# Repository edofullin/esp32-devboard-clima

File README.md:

# ESP32-Clima

This repository contains the design and production files that I used to build by own ESP32-based OpenTherm* and ON/OFF thermostats.

The devices is based on a ESP32-S3 microcontroller, and can include *exclusively* a OpenTherm driver circuit or a latching on/off relay to drive the boiler. 
Optionally, a BME280 sensor can be soldered onto the board in order to measure temperature, humidity and pressure (and use them for control).

## Schematic

## PCB Design

## Final Result (OpenTherm version, no BME280)

Mounted by me by hand, imperfect but functioning. 

## Disclaimers

I'm an not a PCB designer / electronics professional, everything here is provided for free and the user assumes all resposibilities of what they do with the material.
This material comes AS-IS with ABSOLUTELY NO WARRANTY.

*I'm **NOT** affiliated with the [OpenTherm Association](https://www.opentherm.eu/) in any way, the circuit has **only** been tested by me on my own boiler and is not guaranteed to work on every boiler.

The OpenTherm circuit part is heavily inspired by [this](https://electronics.stackexchange.com/questions/466720/how-does-this-circuit-work-opentherm) StackExchange post.

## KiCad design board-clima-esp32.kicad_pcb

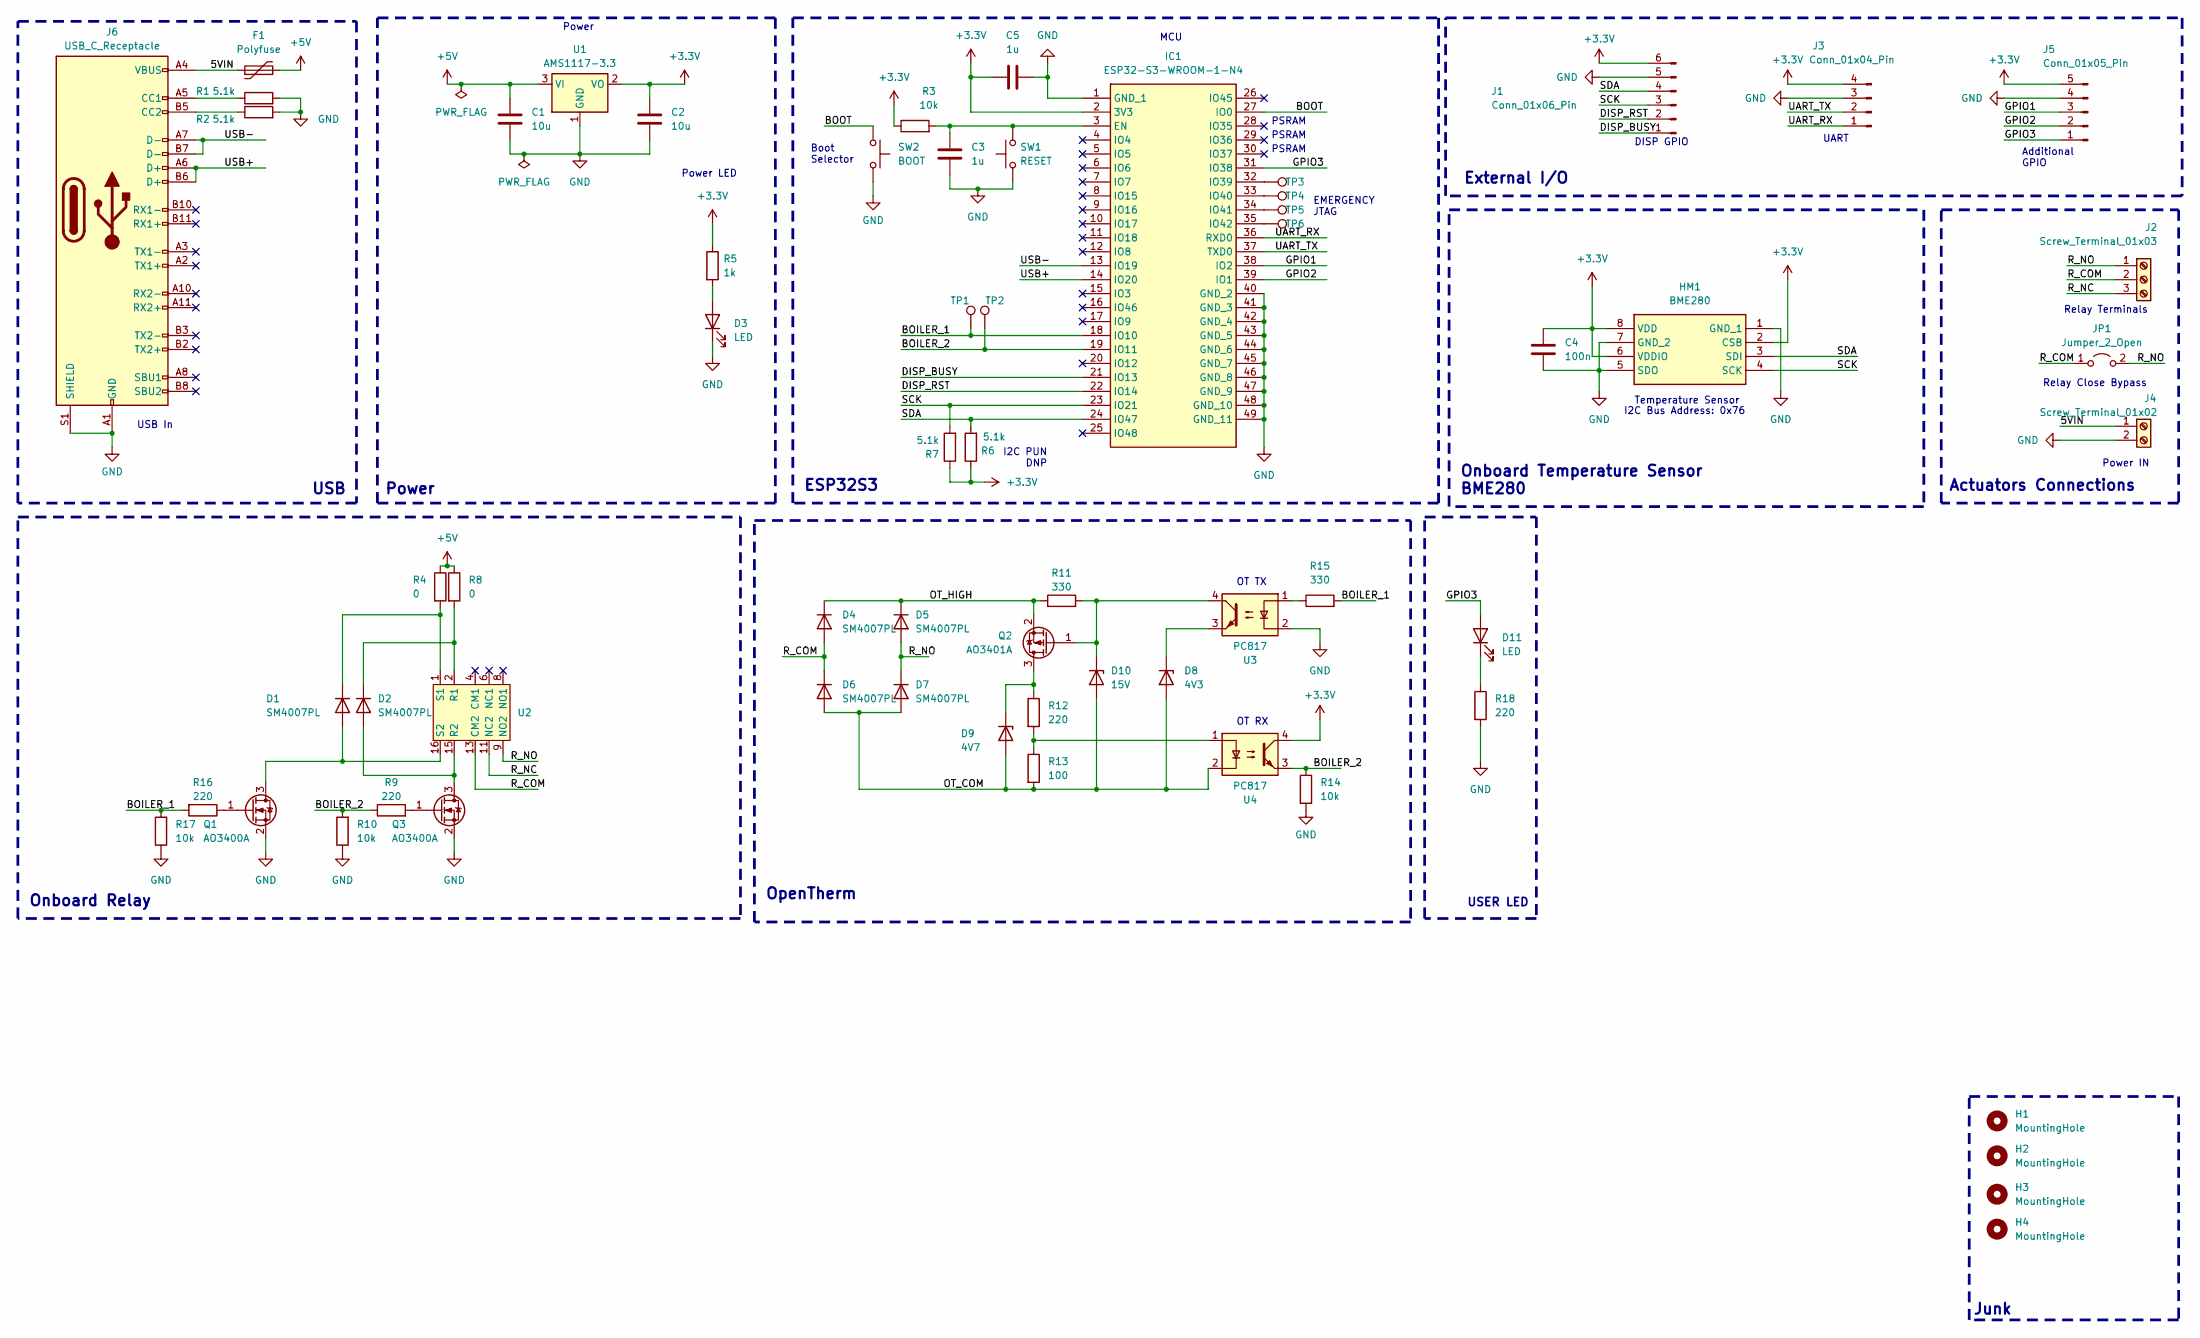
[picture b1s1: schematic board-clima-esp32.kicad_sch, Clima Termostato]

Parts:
C1, C2: 10u; C_0805_2012Metric; Manufacturer_Part_Number CL21A106KAYNNNE; LCSC C15850
C3: 1u; C_0805_2012Metric; Manufacturer_Part_Number CL21B105KBFNNNE; LCSC C28323
C4: 100n; C_0805_2012Metric; Manufacturer_Part_Number CC0805KRX7R9BB104; LCSC C49678
C5: 1u; C_0805_2012Metric
D1, D2, D4, D5, D6, D7: SM4007PL; D_SOD-123F
D3: LED; LED_0805_2012Metric; Manufacturer_Part_Number NCD0805R1; LCSC C84256
D8: 4V3; D_SOD-123
D9: 4V7; D_SOD-123
D10: 15V; D_SOD-123
D11: LED; LED_0805_2012Metric
F1: Polyfuse; Fuse_1812_4532Metric_Pad1.30x3.40mm_HandSolder; Manufacturer_Part_Number BSMD1812-200-30V; LCSC C960026
H1, H2, H3, H4: MountingHole; MountingHole_2.5mm
HM1: BME280; Mouser Part Number 262-BME280
IC1: ESP32-S3-WROOM-1-N4; ESP32S3WROOM1N8R8; Mouser Part Number 356-EP32S3WROOM1N8R8
J1: Conn_01x06_Pin; PinHeader_1x06_P2.54mm_Vertical
J2: Screw_Terminal_01x03; XYEK500-5.08-3P; Manufacturer_Part_Number XYEK500-5.08-3P
J3: Conn_01x04_Pin; PinHeader_1x04_P2.54mm_Vertical
J4: Screw_Terminal_01x02; XYEK500-5.08-2P
J5: Conn_01x05_Pin; PinHeader_1x05_P2.54mm_Vertical
J6: USB_C_Receptacle; HRO_TYPE-C-31-M-12; Manufacturer_Part_Number TYPE-C-31-M-12; LCSC C165948
JP1: Jumper_2_Open; TestPoint_2Pads_Pitch2.54mm_Drill0.8mm
Q1, Q3: AO3400A; SOT-23
Q2: AO3401A; SOT-23
R1, R2, R6, R7: 5.1k; R_0805_2012Metric; Manufacturer_Part_Number 0805W8F5101T5E; LCSC C17673
R3: 10k; R_0805_2012Metric; Manufacturer_Part_Number 0805W8F1002T5E; LCSC C17414
R4, R8: 0; R_0805_2012Metric
R5: 1k; R_0805_2012Metric; Manufacturer_Part_Number 0805W8F2200T5E; LCSC C17557
R9, R12, R16, R18: 220; R_0805_2012Metric
R10, R14, R17: 10k; R_0805_2012Metric
R11, R15: 330; R_0805_2012Metric
R13: 100; R_0805_2012Metric
SW1: RESET; SW_Push_1P1T_XKB_TS-1187A; Manufacturer_Part_Number TS-1187A-B-A-B; LCSC C318884
SW2: BOOT; SW_Push_1P1T_XKB_TS-1187A; Manufacturer_Part_Number TS-1187A-B-A-B; LCSC C318884
TP1, TP2, TP3, TP4, TP5, TP6: TestPoint; TestPoint_Pad_D1.0mm
U1: AMS1117-3.3; SOT-223-3_TabPin2; Manufacturer_Part_Number 0805W8F5101T5E; LCSC C6186
U2: HFD2-00X-M-L2
U3, U4: PC817; DIP-4_W7.62mm

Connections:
+3.3V: C2.1, C4.1, C5.1, HM1.2 (CSB), HM1.6 (VDDIO), HM1.8 (VDD), IC1.2 (3V3), J1.6, J3.4, J5.5, R3.1, R5.1, R6.1, R7.1, U1.2 (VO), U4.4
+5V: C1.1, F1.2, R4.1, R8.1, U1.3 (VI)
/5VIN: F1.1, J4.1, J6.A4 (VBUS), J6.A9 (VBUS), J6.B4 (VBUS), J6.B9 (VBUS)
/BOILER_1: IC1.18 (IO10), R15.2, R16.2, R17.2, TP1.1; also elsewhere on the board
/BOILER_2: IC1.19 (IO11), R9.1, R10.2, R14.1, TP2.1, U4.3; also elsewhere on the board
/BOOT: IC1.27 (IO0), SW2.1
/DISP_BUSY: IC1.21 (IO13), J1.1
/DISP_RST: IC1.22 (IO14), J1.2
/GPIO1: IC1.38 (IO2), J5.3
/GPIO2: IC1.39 (IO1), J5.2
/GPIO3: D11.2 (A), IC1.31 (IO38), J5.1
/OT_COM: D6.2 (A), D7.2 (A), D8.2 (A), D9.2 (A), D10.2 (A), R13.2, U4.2
/OT_HIGH: D4.1 (K), D5.1 (K), Q2.2 (S), R11.1
/R_COM: D4.2 (A), D6.1 (K), J2.2, JP1.1 (A), U2.13 (CM2)
/R_NC: J2.3, U2.11 (NC2)
/R_NO: D5.2 (A), D7.1 (K), J2.1, JP1.2 (B), U2.9 (NO2)
/SCK: HM1.4 (SCK), IC1.23 (IO21), J1.3, R7.2
/SDA: HM1.3 (SDI), IC1.24 (IO47), J1.4, R6.2
/UART_RX: IC1.36 (RXD0), J3.1
/UART_TX: IC1.37 (TXD0), J3.2
/USB+: IC1.14 (IO20), J6.A6 (D+), J6.B6 (D+)
/USB-: IC1.13 (IO19), J6.A7 (D-), J6.B7 (D-)
GND: C1.2, C2.2, C3.2, C4.2, C5.2, D3.1 (K), HM1.1 (GND_1), HM1.5 (SDO), HM1.7 (GND_2), IC1.1 (GND_1), IC1.40 (GND_2), IC1.41 (GND_3), IC1.42 (GND_4), IC1.43 (GND_5), IC1.44 (GND_6), IC1.45 (GND_7), IC1.46 (GND_8), IC1.47 (GND_9), IC1.48 (GND_10), IC1.49 (GND_11), J1.5, J3.3, J4.2, J5.4, J6.A1 (GND), J6.A12 (GND), J6.B1 (GND), J6.B12 (GND), J6.S1 (SHIELD), Q1.2 (S), Q3.2 (S), R1.2, R2.2, R10.1, R14.2, R17.1, R18.2, SW1.1, SW2.2, U1.1 (GND), U3.2
unnamed: D1.2 (A), Q1.3 (D), U2.16 (S2)
unnamed: D1.1 (K), R4.2, U2.1 (S1)
unnamed: D2.2 (A), Q3.3 (D), U2.15 (R2)
unnamed: D2.1 (K), R8.2, U2.2 (R1)
unnamed: D3.2 (A), R5.2
unnamed: D8.1 (K), U3.3
unnamed: D9.1 (K), Q2.3 (D), R12.1
unnamed: D10.1 (K), Q2.1 (G), R11.2, U3.4
unnamed: D11.1 (K), R18.1
unnamed: C3.1, IC1.3 (EN), R3.2, SW1.2
unnamed: IC1.32 (IO39), TP3.1
unnamed: IC1.33 (IO40), TP4.1
unnamed: IC1.34 (IO41), TP5.1
unnamed: IC1.35 (IO42), TP6.1
unnamed: J6.A5 (CC1), R1.1
unnamed: J6.B5 (CC2), R2.1
unnamed: Q1.1 (G), R16.1
unnamed: Q3.1 (G), R9.2
unnamed: R12.2, R13.1, U4.1
unnamed: R15.1, U3.1

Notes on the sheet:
OpenTherm
ESP32S3
MCU
Junk
Onboard Temperature Sensor BME280
Actuators Connections
I2C PUN DNP
PSRAM
Power IN
UART
Relay Close Bypass
Additional GPIO
EMERGENCY JTAG
Boot Selector
External I/O
USER LED
Power
Onboard Relay
OT TX
Temperature Sensor
USB
DISP GPIO
USB In
OT RX
I2C Bus Address: 0x76
Relay Terminals
Power LED

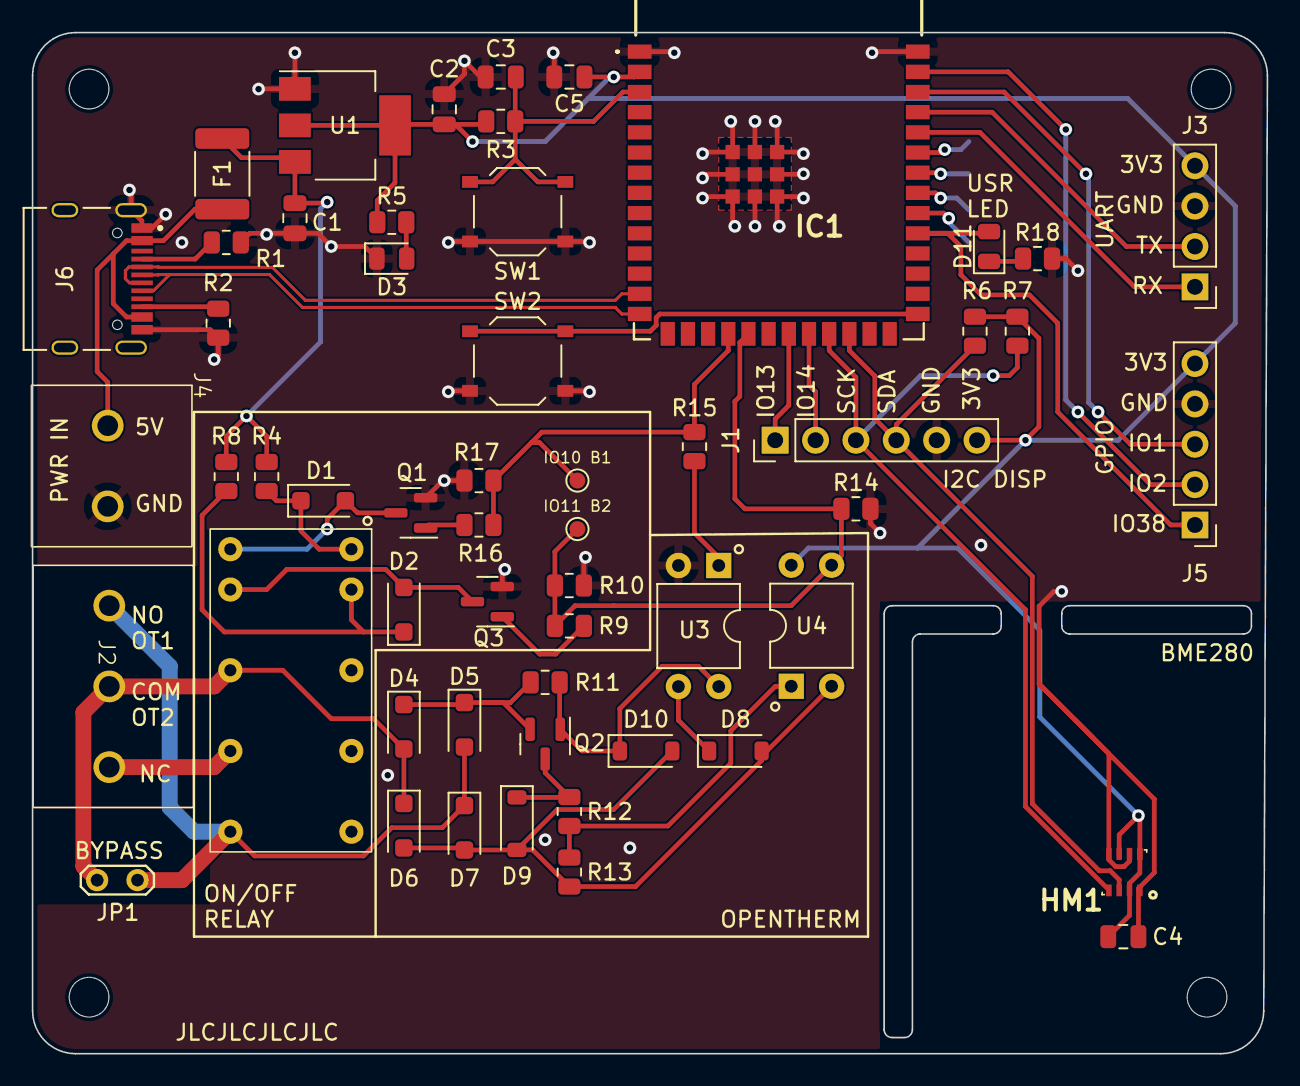
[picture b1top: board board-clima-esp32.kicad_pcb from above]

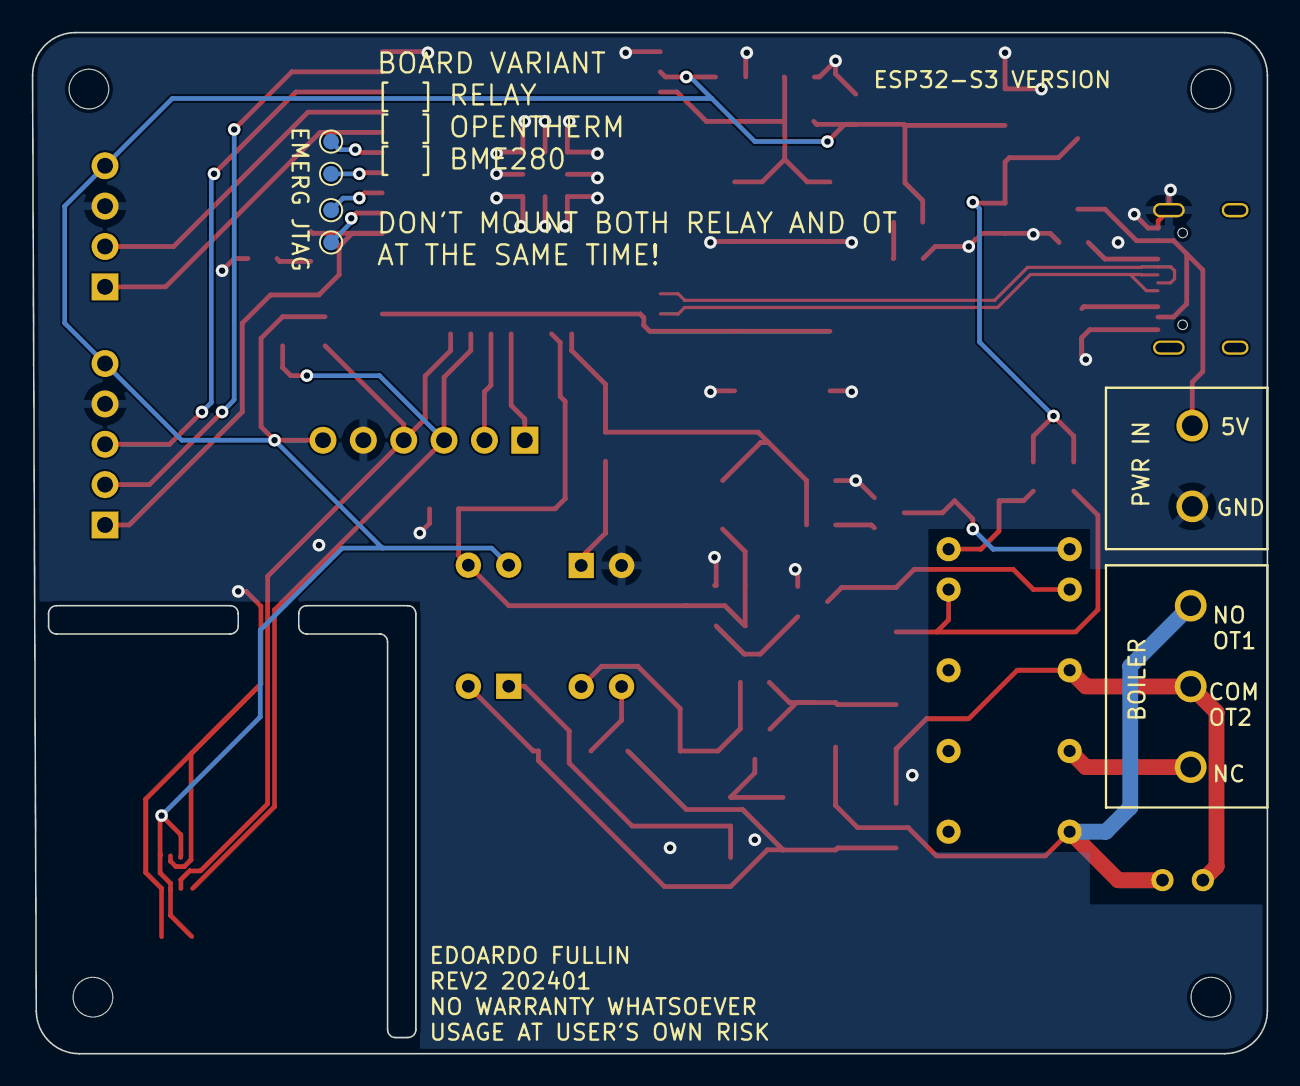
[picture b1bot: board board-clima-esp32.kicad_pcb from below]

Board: 2 copper layers, 77.7 x 64.3 mm, 63 parts (4 on the bottom side), 43 nets.

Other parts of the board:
IO10 B1, IO11 B2: TestPoint; TestPoint_Pad_D1.0mm

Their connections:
/BOILER_1: IO10 B1.1; also elsewhere on the board
/BOILER_2: IO11 B2.1; also elsewhere on the board

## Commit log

2023-10-22 libs, basic power
2023-10-22 edits
2023-10-24 sensor, relay sym footprint
2023-10-24 schematic ok
2023-10-24 fucking via clearences
2023-10-25 usb pads, via sizes
2023-10-25 moved bme280
2023-10-25 should be done
2023-10-27 editing stuff again
2023-10-28 edit to get jlc assembly
2023-10-29 component edits, terminalblock footprint
2023-10-29 was about to fuck everything up
2023-10-29 cleanup and some helper in schematic
2023-10-31 added bypass jumper
2023-12-10 refactor schematic
2023-12-12 spice for opentherm, schematics mod
2023-12-27 OT schematic, relay spice
2023-12-28 rev2 schematic
2023-12-29 pcb rev2 placement
2023-12-29 New J1 connector location
2023-12-29 Cleanup pcb layout for easier routing
2023-12-29 rev2 routing
2023-12-29 silkscreen
2023-12-29 Moved BME and DISP connector
2023-12-30 drc passes
2024-01-03 new PWR connector, front copper pour
2024-01-10 final corrections
2024-01-10 drc pass
2024-01-10 flipped relay
2024-02-15 relay was flipped :(
2024-02-15 docs
2024-02-15 add disclaimer
